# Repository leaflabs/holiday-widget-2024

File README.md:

# Holiday Widget

Basic startup project for NUCLEO-L053R8 board. 

Source code lives in firmware.

The build directory holds all .o files for compliation. The output binary is build/blink.elf. This folder is generated at compilation time and will not exist upon cloning the repository.

Include holds all user created .h files. For the HAL to work, the stm3l0xx_hal_conf_template.h file needs to be copied and adjusted as necessary. No changes were made as of now. 

src holds all user created .c files. This project does not use the c library so some builtin functions needed to be defined, namely __libc_init_array, memset and memcpy. main.c holds the main function and the basic code to blink the LD2 LED at a different speed when the B1 button is pressed.

linker_script.ld defines how the binary should be setup.  
  
Makefile has two main targets: build/blink.elf and upload  
build/blink.elf is also called by just calling 'make' and creates the .elf file. upload sends the .elf file to the Nucleo board.

The STM32CubeL0 and SmallPrintf folders are submodules for this repo. When cloning the project, run 'git submodule update --init --recursive' to create the folder.

Overall steps to get project and upload to nucleo board:
```
git clone --recursive <repo name> 
git submodule update --init --recursive
make
make upload
```

Dependencies:
* STM32CubeL0 at version v1.12.2
* eyalroz/printf at version v6.2.0-b1

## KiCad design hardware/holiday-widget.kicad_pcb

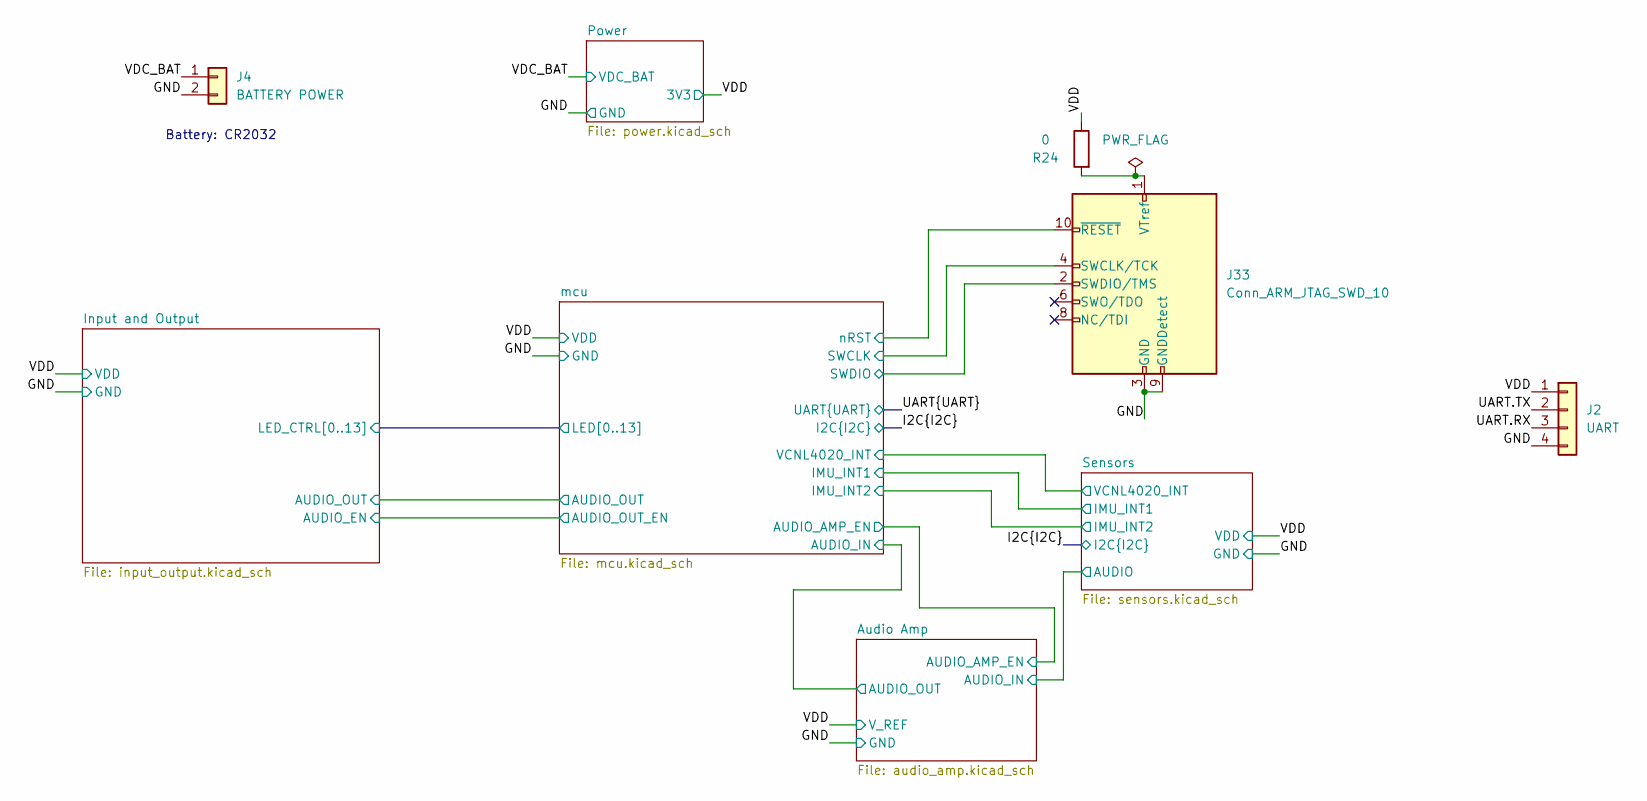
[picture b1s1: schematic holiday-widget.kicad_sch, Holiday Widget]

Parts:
J2: UART; PinHeader_1x04_P2.00mm_Vertical
J4: BATTERY POWER; MPD_BC2032-E2
J33: Conn_ARM_JTAG_SWD_10; PinHeader_2x05_P1.27mm_Vertical
R24: 0; R_0402_1005Metric; MPN RC0402JR-070RL

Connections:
/GND: J2.4, J4.2, J33.3 (GND), J33.5 (GND), J33.9 (GNDDetect); also elsewhere on the board
/UART.RX: J2.3; also elsewhere on the board
/UART.TX: J2.2; also elsewhere on the board
/VDC_BAT: J4.1; also elsewhere on the board
/VDD: J2.1, R24.1; also elsewhere on the board
/mcu/SWCLK: J33.4 (SWCLK/TCK); also elsewhere on the board
/mcu/SWDIO: J33.2 (SWDIO/TMS); also elsewhere on the board
/mcu/nRST: J33.10 (~RESET); also elsewhere on the board
unnamed: J33.1 (VTref), R24.2

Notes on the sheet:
Battery: CR2032

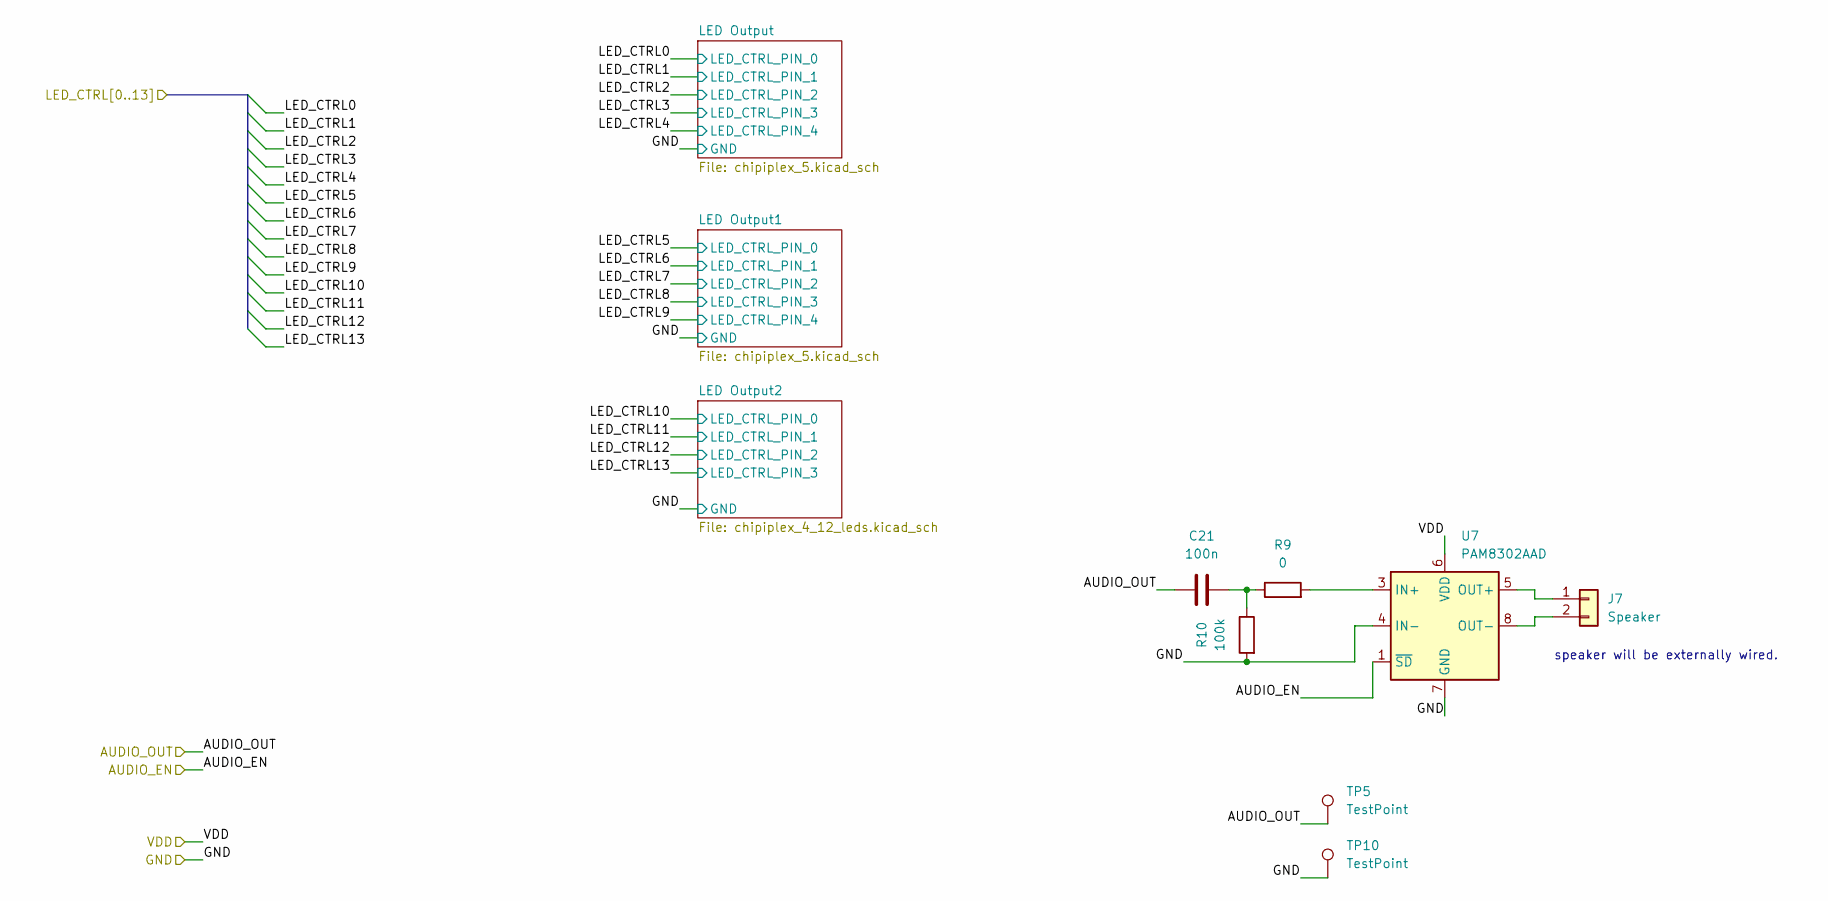
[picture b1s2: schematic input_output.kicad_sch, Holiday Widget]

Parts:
C21: 100n; C_0402_1005Metric; MPN CL05A104KA5NNNC
J7: Speaker; SPKR_AST-01508MR-WT-R
R9: 0; R_0402_1005Metric; MPN RC0402JR-070RL
R10: 100k; R_0402_1005Metric; MPN RC0402FR-07100KL
TP5, TP10: TestPoint; TestPoint_0.5mm_1mm
U7: PAM8302AAD; SSOP-8_2.95x2.8mm_P0.65mm; MPN PAM8302AADCR

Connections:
/GND: R10.2, TP10.1, U7.4 (IN-), U7.7 (GND); also elsewhere on the board
/Input and Output/AUDIO_EN: U7.1 (~SD); also elsewhere on the board
/Input and Output/AUDIO_OUT: C21.1, TP5.1; also elsewhere on the board
/VDD: U7.6 (VDD); also elsewhere on the board
unnamed: C21.2, R9.1, R10.1
unnamed: J7.1, U7.5 (OUT+)
unnamed: J7.2, U7.8 (OUT-)
unnamed: R9.2, U7.3 (IN+)

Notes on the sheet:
speaker will be externally wired.

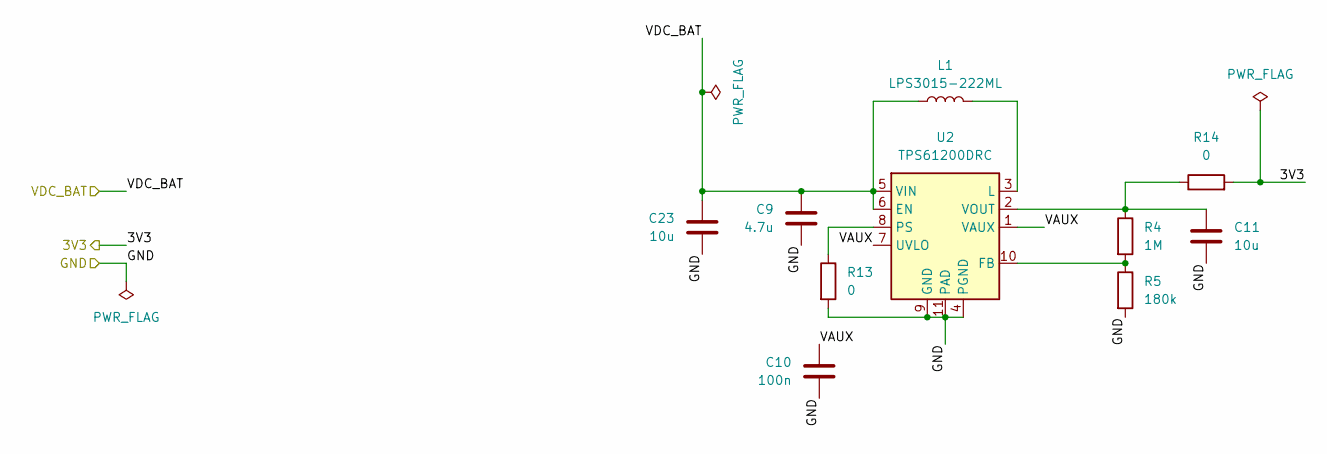
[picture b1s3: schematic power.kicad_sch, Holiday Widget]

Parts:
C9: 4.7u; C_0402_1005Metric; MPN CL05A475MP5NRNC
C10: 100n; C_0402_1005Metric; MPN CL05A104KA5NNNC
C11, C23: 10u; C_0603_1608Metric_Pad1.08x0.95mm_HandSolder; MPN CL10A106MQ8NNNC
L1: LPS3015-222ML; L_Coilcraft_LPS3010; MPN LPS3015-222MRC
R4: 1M; R_0402_1005Metric; MPN RC0402FR-071ML
R5: 180k; R_0402_1005Metric; MPN RC0402JR-07180KL
R13, R14: 0; R_0402_1005Metric; MPN RC0402JR-070RL
U2: TPS61200DRC; Texas_S-PVSON-N10_ThermalVias; MPN TPS61200DRCT

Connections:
/GND: C9.2, C10.2, C11.2, C23.2, R5.2, R13.2, U2.4 (PGND), U2.9 (GND), U2.11 (PAD); also elsewhere on the board
/Power/VAUX: C10.1, U2.1 (VAUX), U2.7 (UVLO)
/VDC_BAT: C9.1, C23.1, L1.1, U2.5 (VIN), U2.6 (EN); also elsewhere on the board
/VDD: R14.2; also elsewhere on the board
unnamed: R4.2, R5.1, U2.10 (FB)
unnamed: L1.2, U2.3 (L)
unnamed: R13.1, U2.8 (PS)
unnamed: C11.1, R4.1, R14.1, U2.2 (VOUT)

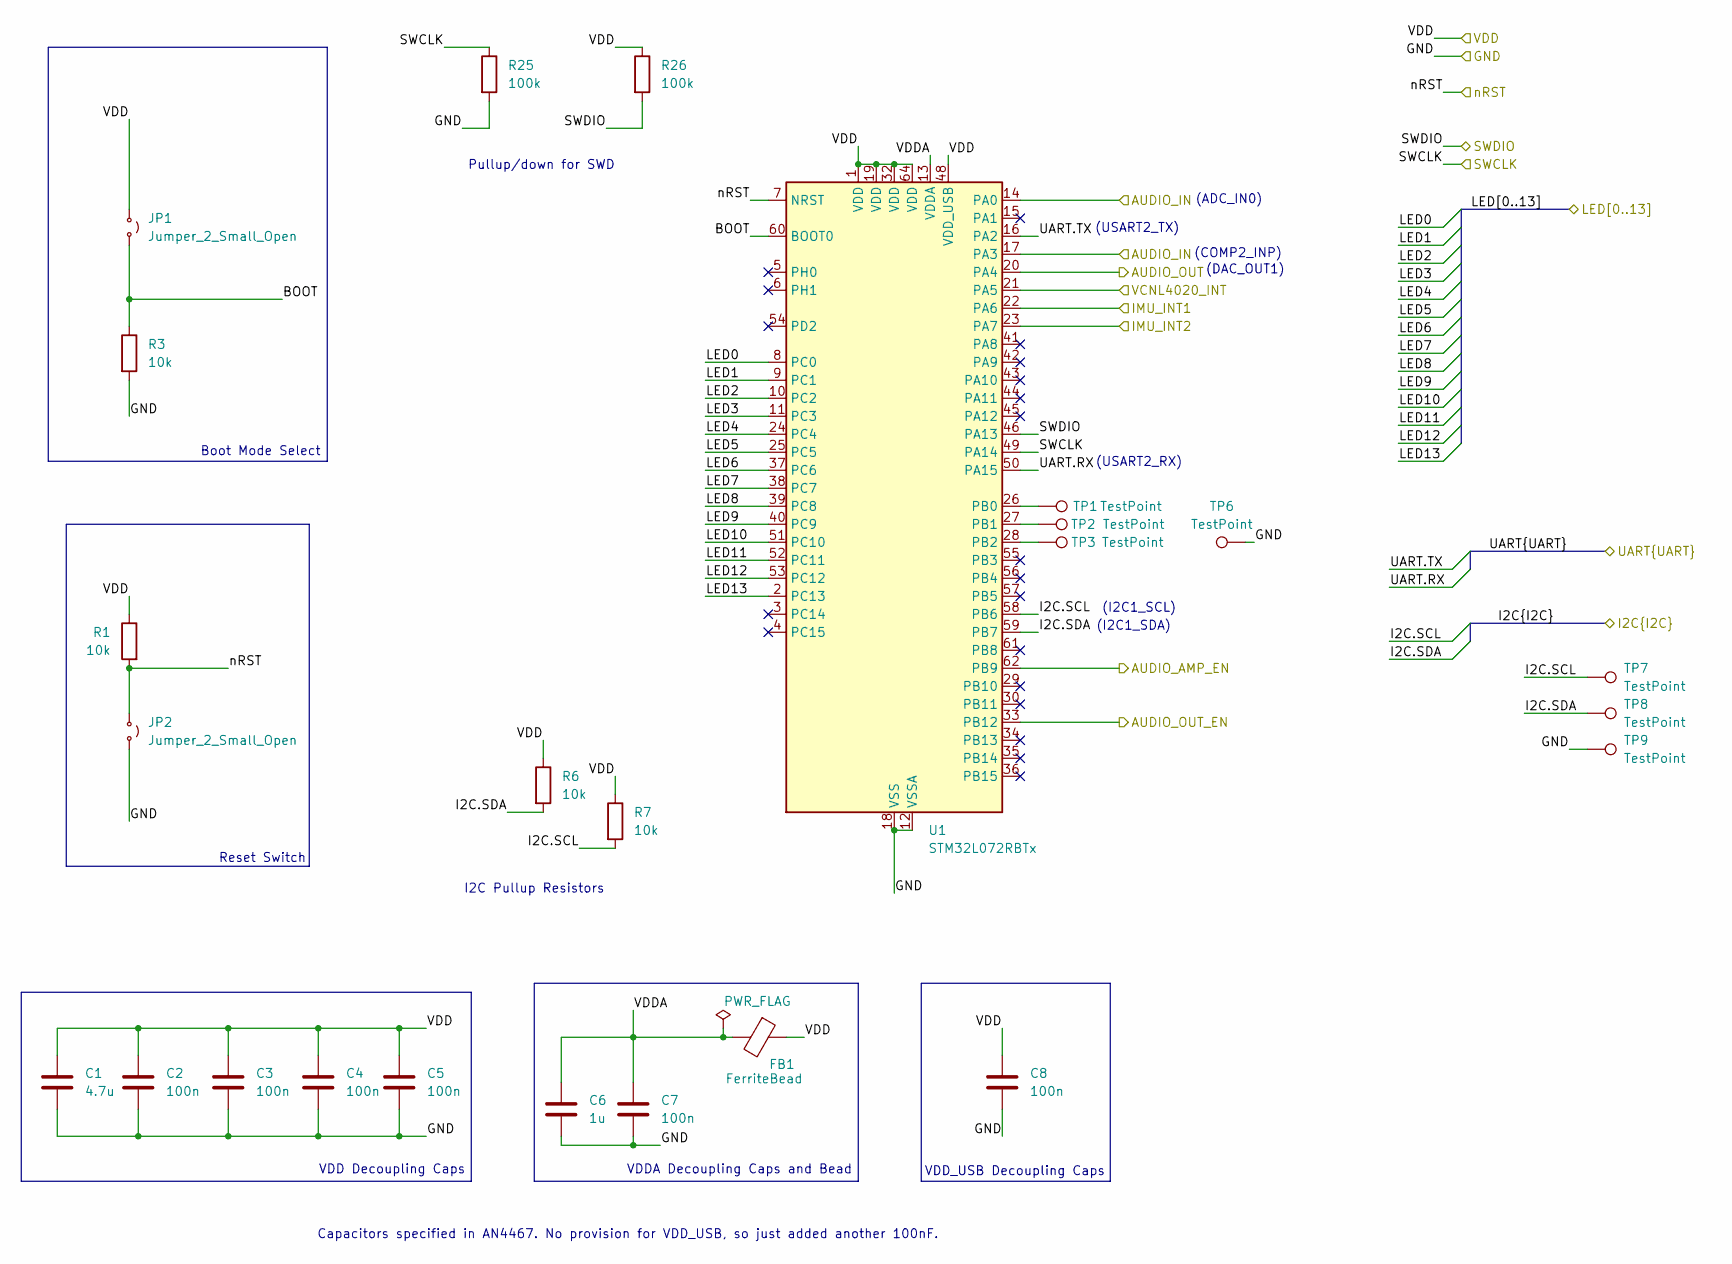
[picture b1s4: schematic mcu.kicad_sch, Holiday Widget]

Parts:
C1: 4.7u; C_0402_1005Metric; MPN CL05A475MP5NRNC
C2, C3, C4, C5, C7, C8: 100n; C_0402_1005Metric; MPN CL05A104KA5NNNC
C6: 1u; C_0603_1608Metric_Pad1.08x0.95mm_HandSolder; MPN CL05A105KO5NNNC
FB1: FerriteBead; C_0603_1608Metric_Pad1.08x0.95mm_HandSolder; MPN 742792662
JP1, JP2: Jumper_2_Small_Open; SolderJumper-2_P1.3mm_Open_RoundedPad1.0x1.5mm
R1, R3, R6, R7: 10k; R_0402_1005Metric; MPN RC0402FR-0710KL
R25, R26: 100k; R_0402_1005Metric; MPN RC0402FR-07100KL
TP1, TP2, TP3, TP6, TP7, TP8, TP9: TestPoint; TestPoint_0.5mm_1mm
U1: STM32L072RBTx; LQFP-64_10x10mm_P0.5mm; MPN STM32L072RBT6

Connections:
/Audio Amp/AUDIO_AMP_EN: U1.62 (PB9); also elsewhere on the board
/Audio Amp/AUDIO_OUT: U1.14 (PA0), U1.17 (PA3); also elsewhere on the board
/GND: C1.2, C2.2, C3.2, C4.2, C5.2, C6.2, C7.2, C8.2, JP2.2 (B), R3.2, R25.2, TP6.1, TP9.1, U1.12 (VSSA), U1.18 (VSS), U1.31 (VSS), U1.47 (VSS), U1.63 (VSS); also elsewhere on the board
/I2C.SCL: R7.2, TP7.1, U1.58 (PB6); also elsewhere on the board
/I2C.SDA: R6.2, TP8.1, U1.59 (PB7); also elsewhere on the board
/Input and Output/AUDIO_EN: U1.33 (PB12); also elsewhere on the board
/Input and Output/AUDIO_OUT: U1.20 (PA4); also elsewhere on the board
/Sensors/IMU_INT1: U1.22 (PA6); also elsewhere on the board
/Sensors/IMU_INT2: U1.23 (PA7); also elsewhere on the board
/Sensors/VCNL4020_INT: U1.21 (PA5); also elsewhere on the board
/UART.RX: U1.50 (PA15); also elsewhere on the board
/UART.TX: U1.16 (PA2); also elsewhere on the board
/VDD: C1.1, C2.1, C3.1, C4.1, C5.1, C8.1, FB1.1, JP1.1 (A), R1.1, R6.1, R7.1, R26.1, U1.1 (VDD), U1.19 (VDD), U1.32 (VDD), U1.48 (VDD_USB), U1.64 (VDD); also elsewhere on the board
/mcu/BOOT: JP1.2 (B), R3.1, U1.60 (BOOT0)
/mcu/LED0: U1.8 (PC0); also elsewhere on the board
/mcu/LED1: U1.9 (PC1); also elsewhere on the board
/mcu/LED2: U1.10 (PC2); also elsewhere on the board
/mcu/LED3: U1.11 (PC3); also elsewhere on the board
/mcu/LED4: U1.24 (PC4); also elsewhere on the board
/mcu/LED5: U1.25 (PC5); also elsewhere on the board
/mcu/LED6: U1.37 (PC6); also elsewhere on the board
/mcu/LED7: U1.38 (PC7); also elsewhere on the board
/mcu/LED8: U1.39 (PC8); also elsewhere on the board
/mcu/LED9: U1.40 (PC9); also elsewhere on the board
/mcu/LED10: U1.51 (PC10); also elsewhere on the board
/mcu/LED11: U1.52 (PC11); also elsewhere on the board
/mcu/LED12: U1.53 (PC12); also elsewhere on the board
/mcu/LED13: U1.2 (PC13); also elsewhere on the board
/mcu/SWCLK: R25.1, U1.49 (PA14); also elsewhere on the board
/mcu/SWDIO: R26.2, U1.46 (PA13); also elsewhere on the board
/mcu/VDDA: C6.1, C7.1, FB1.2, U1.13 (VDDA)
/mcu/nRST: JP2.1 (A), R1.2, U1.7 (NRST); also elsewhere on the board
unnamed: TP1.1, U1.26 (PB0)
unnamed: TP2.1, U1.27 (PB1)
unnamed: TP3.1, U1.28 (PB2)

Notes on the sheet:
Capacitors specified in AN4467. No provision for VDD_USB, so just added another 100nF.
Reset Switch
I2C Pullup Resistors
(COMP2_INP)
VDD_USB Decoupling Caps
VDDA Decoupling Caps and Bead
(ADC_IN0)
(USART2_TX)
Boot Mode Select
Pullup/down for SWD
VDD Decoupling Caps
(I2C1_SCL)
(USART2_RX)
(DAC_OUT1)
(I2C1_SDA)

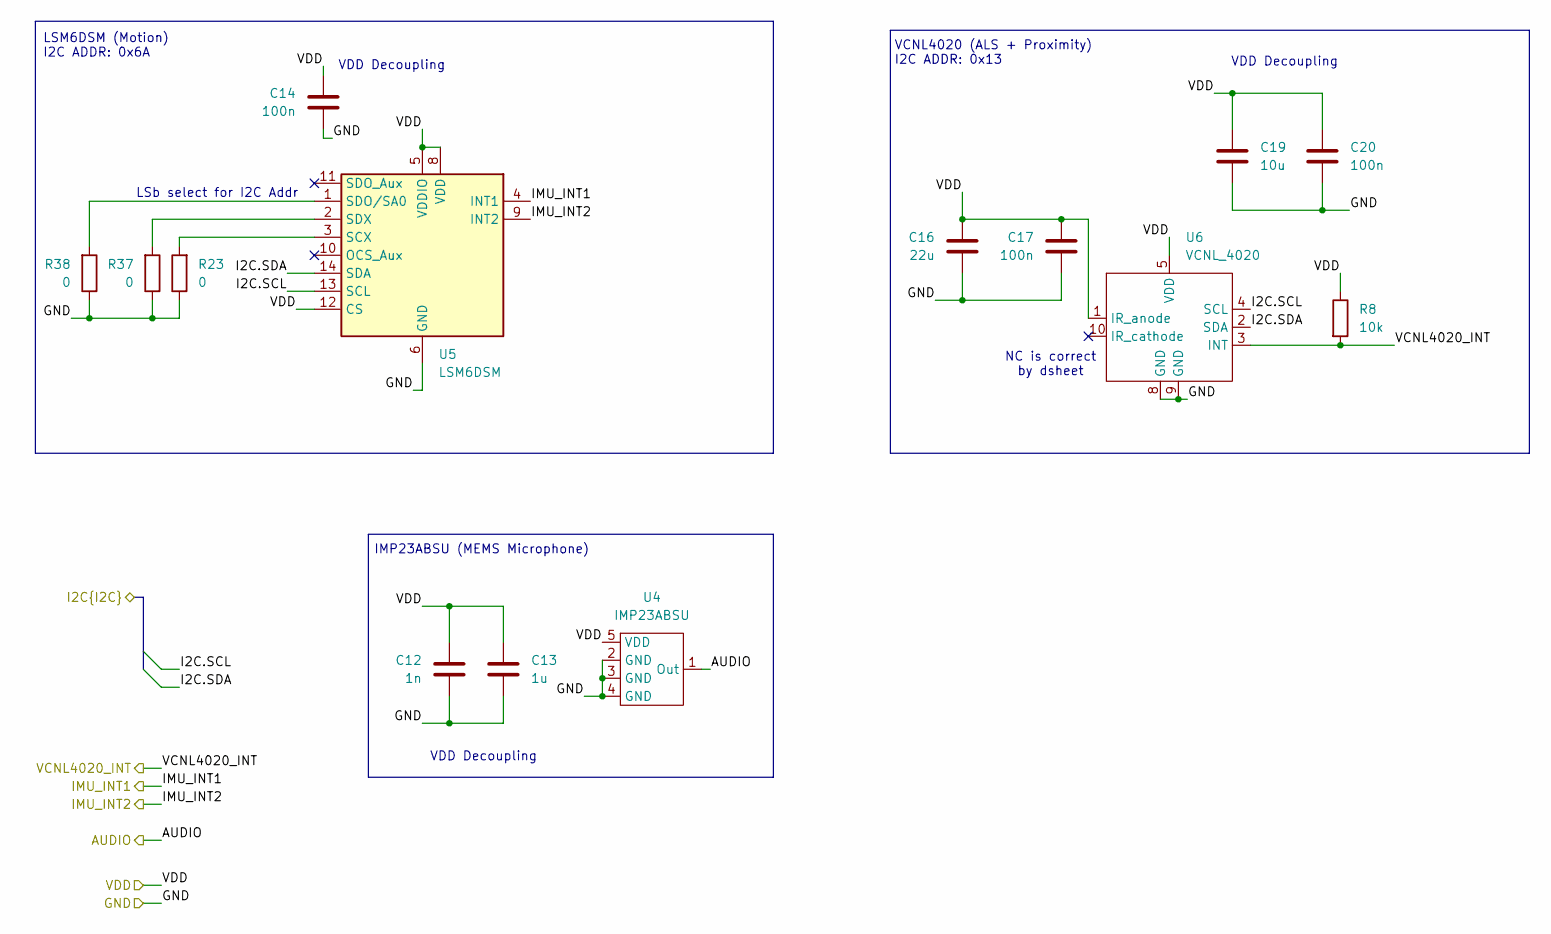
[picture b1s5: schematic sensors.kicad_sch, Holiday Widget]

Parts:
C12: 1n; C_0402_1005Metric; MPN C0402C102K4RACTU
C13: 1u; C_0603_1608Metric_Pad1.08x0.95mm_HandSolder; MPN CL05A105KO5NNNC
C14, C17, C20: 100n; C_0402_1005Metric; MPN CL05A104KA5NNNC
C16: 22u; C_0603_1608Metric_Pad1.08x0.95mm_HandSolder; MPN CL10A226MO7JZNC
C19: 10u; C_0603_1608Metric_Pad1.08x0.95mm_HandSolder; MPN CL10A106MQ8NNNC
R8: 10k; R_0402_1005Metric; MPN RC0402FR-0710KL
R23, R37, R38: 0; R_0402_1005Metric; MPN RC0402JR-070RL
U4: IMP23ABSU; RHLGA5_3P5X2P65X0P98_STM; MPN IMP23ABSUTR
U5: LSM6DSM; LGA-14_3x2.5mm_P0.5mm_LayoutBorder3x4y; MPN LSM6DSMTR
U6: VCNL_4020; VCNL4020_SMD; MPN VCNL4020-GS08

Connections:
/Audio Amp/AUDIO_IN: U4.1 (Out); also elsewhere on the board
/GND: C12.2, C13.2, C14.2, C16.2, C17.2, C19.2, C20.2, R23.1, R37.1, R38.1, U4.2 (GND), U4.3 (GND), U4.4 (GND), U5.6 (GND), U5.7 (GND), U6.8 (GND), U6.9 (GND); also elsewhere on the board
/I2C.SCL: U5.13 (SCL), U6.4 (SCL); also elsewhere on the board
/I2C.SDA: U5.14 (SDA), U6.2 (SDA); also elsewhere on the board
/Sensors/IMU_INT1: U5.4 (INT1); also elsewhere on the board
/Sensors/IMU_INT2: U5.9 (INT2); also elsewhere on the board
/Sensors/VCNL4020_INT: R8.2, U6.3 (INT); also elsewhere on the board
/VDD: C12.1, C13.1, C14.1, C16.1, C17.1, C19.1, C20.1, R8.1, U4.5 (VDD), U5.5 (VDDIO), U5.8 (VDD), U5.12 (CS), U6.1 (IR_anode), U6.5 (VDD); also elsewhere on the board
unnamed: R23.2, U5.3 (SCX)
unnamed: R38.2, U5.1 (SDO/SA0)
unnamed: R37.2, U5.2 (SDX)

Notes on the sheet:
IMP23ABSU (MEMS Microphone)
LSb select for I2C Addr
VDD Decoupling
NC is correct by dsheet
LSM6DSM (Motion) I2C ADDR: 0x6A
VCNL4020 (ALS + Proximity) I2C ADDR: 0x13

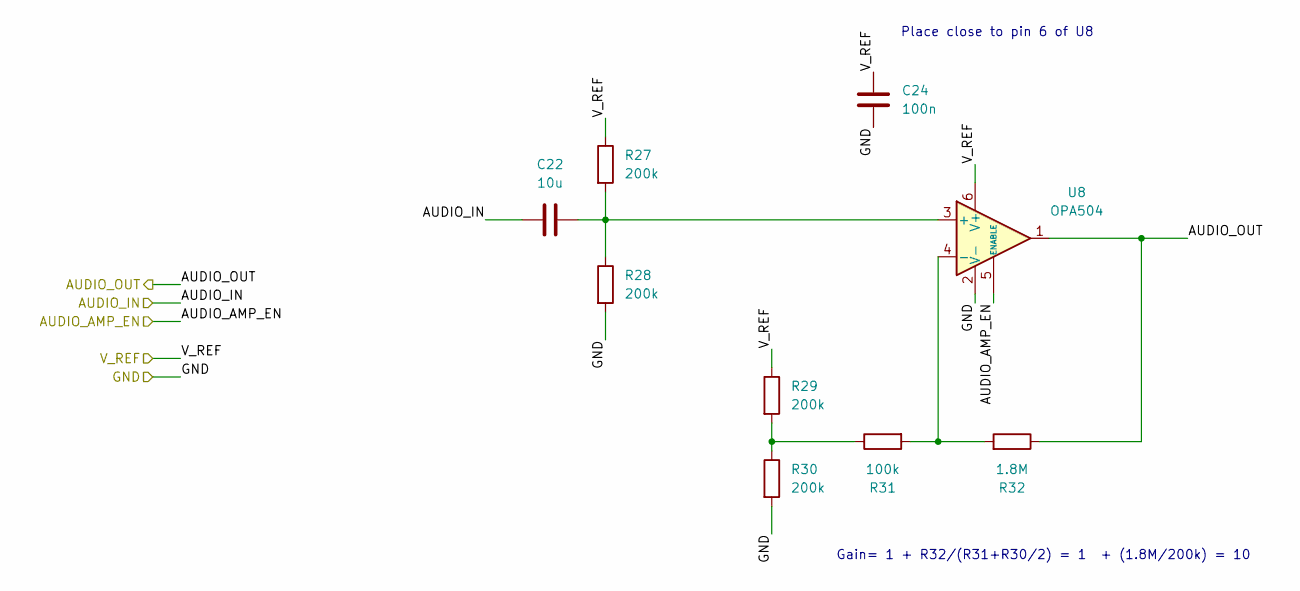
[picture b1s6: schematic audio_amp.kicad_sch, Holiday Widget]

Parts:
C22: 10u; C_0603_1608Metric_Pad1.08x0.95mm_HandSolder; MPN CL10A106MQ8NNNC
C24: 100n; C_0402_1005Metric; MPN CL05A104KA5NNNC
R27, R28, R29, R30: 200k; R_0402_1005Metric; MPN RC0402FR-07200KL
R31: 100k; R_0402_1005Metric; MPN RC0402FR-07100KL
R32: 1.8M; R_0402_1005Metric; MPN RC0402JR-071M8L
U8: OPA504; SOT-23-6

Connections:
/Audio Amp/AUDIO_AMP_EN: U8.5 (ENABLE); also elsewhere on the board
/Audio Amp/AUDIO_IN: C22.1; also elsewhere on the board
/Audio Amp/AUDIO_OUT: R32.1, U8.1; also elsewhere on the board
/GND: C24.1, R28.2, R30.2, U8.2 (V-); also elsewhere on the board
/VDD: C24.2, R27.1, R29.1, U8.6 (V+); also elsewhere on the board
unnamed: R29.2, R30.1, R31.1
unnamed: C22.2, R27.2, R28.1, U8.3 (+)
unnamed: R31.2, R32.2, U8.4 (-)

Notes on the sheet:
Gain= 1 + R32/(R31+R30/2) = 1 + (1.8M/200k) = 10
Place close to pin 6 of U8

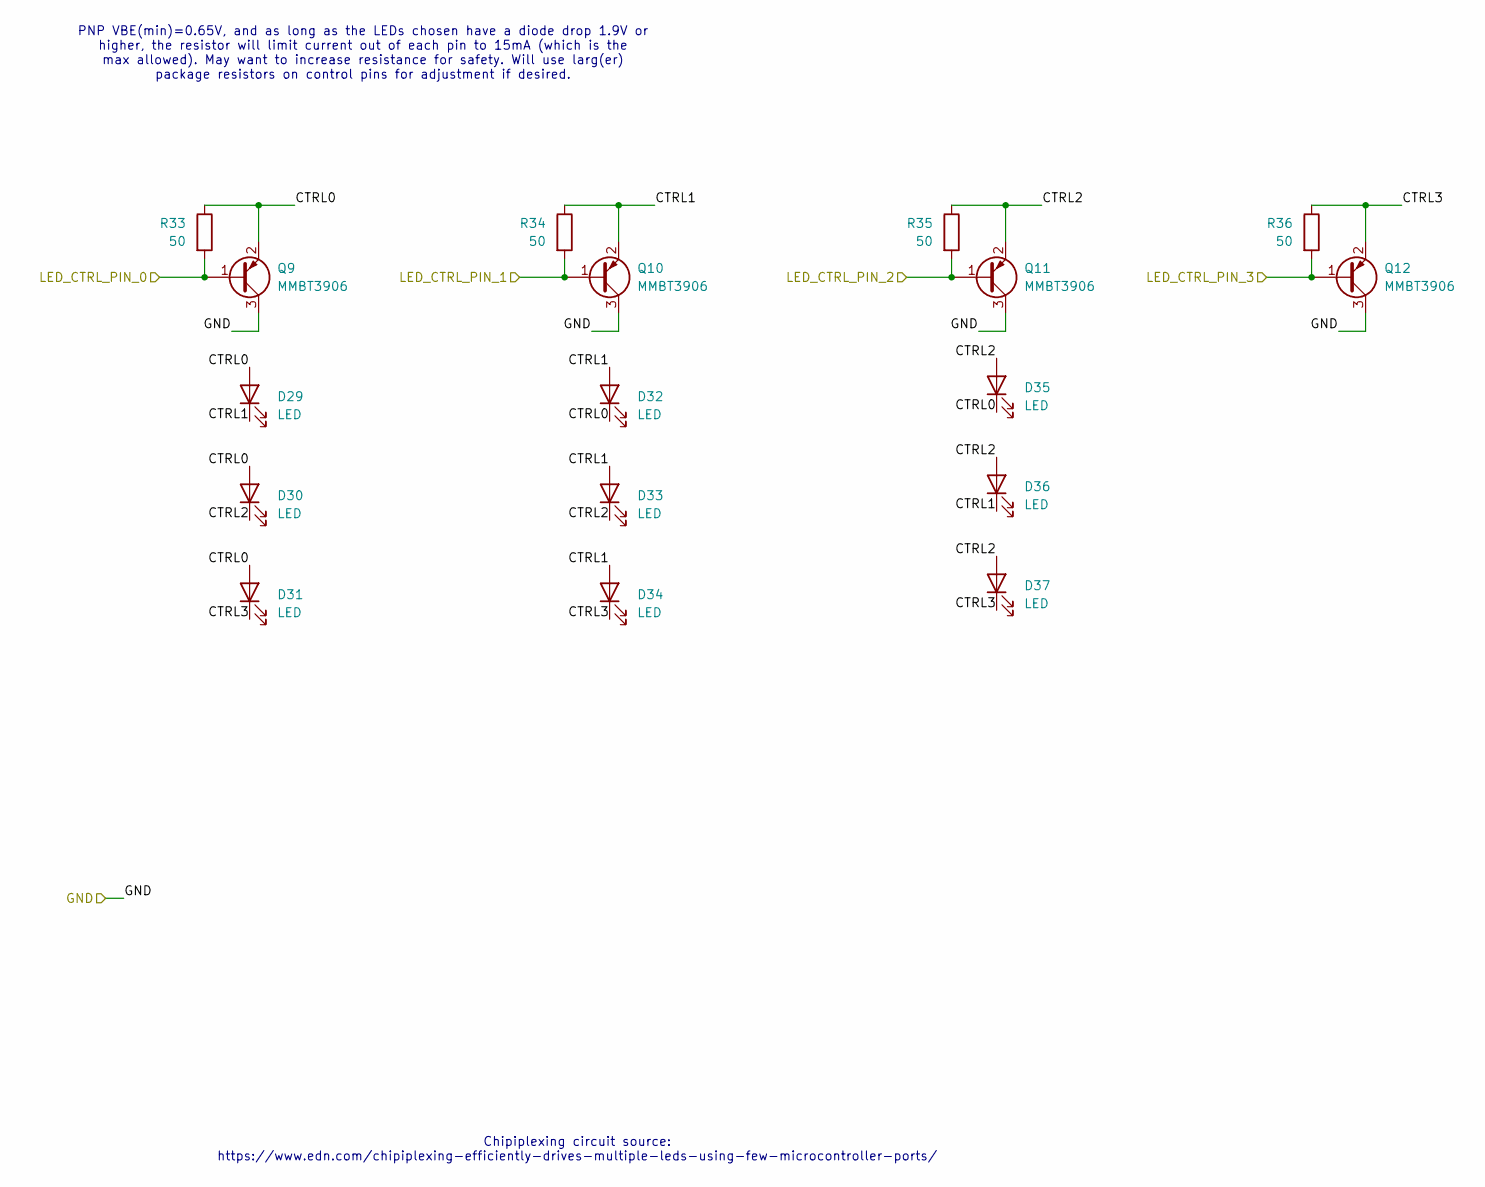
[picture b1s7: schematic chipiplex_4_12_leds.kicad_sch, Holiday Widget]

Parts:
D29, D30, D31, D32, D33, D34, D35, D36, D37: LED; LED_0805_2012Metric_Pad1.15x1.40mm_HandSolder; MPN LTST-C171GKT
Q9, Q10, Q11, Q12: MMBT3906; SOT-23; MPN MMBT3906
R33, R34, R35, R36: 50; R_0402_1005Metric; MPN RC0402JR-0750RL

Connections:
/GND: Q9.3 (C), Q10.3 (C), Q11.3 (C), Q12.3 (C); also elsewhere on the board
/Input and Output/LED Output2/CTRL0: D29.2 (A), D30.2 (A), D31.2 (A), D32.1 (K), D35.1 (K), Q9.2 (E), R33.1
/Input and Output/LED Output2/CTRL1: D29.1 (K), D32.2 (A), D33.2 (A), D34.2 (A), D36.1 (K), Q10.2 (E), R34.1
/Input and Output/LED Output2/CTRL2: D30.1 (K), D33.1 (K), D35.2 (A), D36.2 (A), D37.2 (A), Q11.2 (E), R35.1
/Input and Output/LED Output2/CTRL3: D31.1 (K), D34.1 (K), D37.1 (K), Q12.2 (E), R36.1
/mcu/LED10: Q9.1 (B), R33.2; also elsewhere on the board
/mcu/LED11: Q10.1 (B), R34.2; also elsewhere on the board
/mcu/LED12: Q11.1 (B), R35.2; also elsewhere on the board
/mcu/LED13: Q12.1 (B), R36.2; also elsewhere on the board

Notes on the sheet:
Chipiplexing circuit source: https://www.edn.com/chipiplexing-efficiently-drives-multiple-leds-using-few-microcontroller-ports/
PNP VBE(min)=0.65V, and as long as the LEDs chosen have a diode drop 1.9V or higher, the resistor will limit current out of each pin to 15mA (which is the max allowed). May want to increase resistance for safety. Will use larg(er) package resistors on control pins for adjustment if desired.

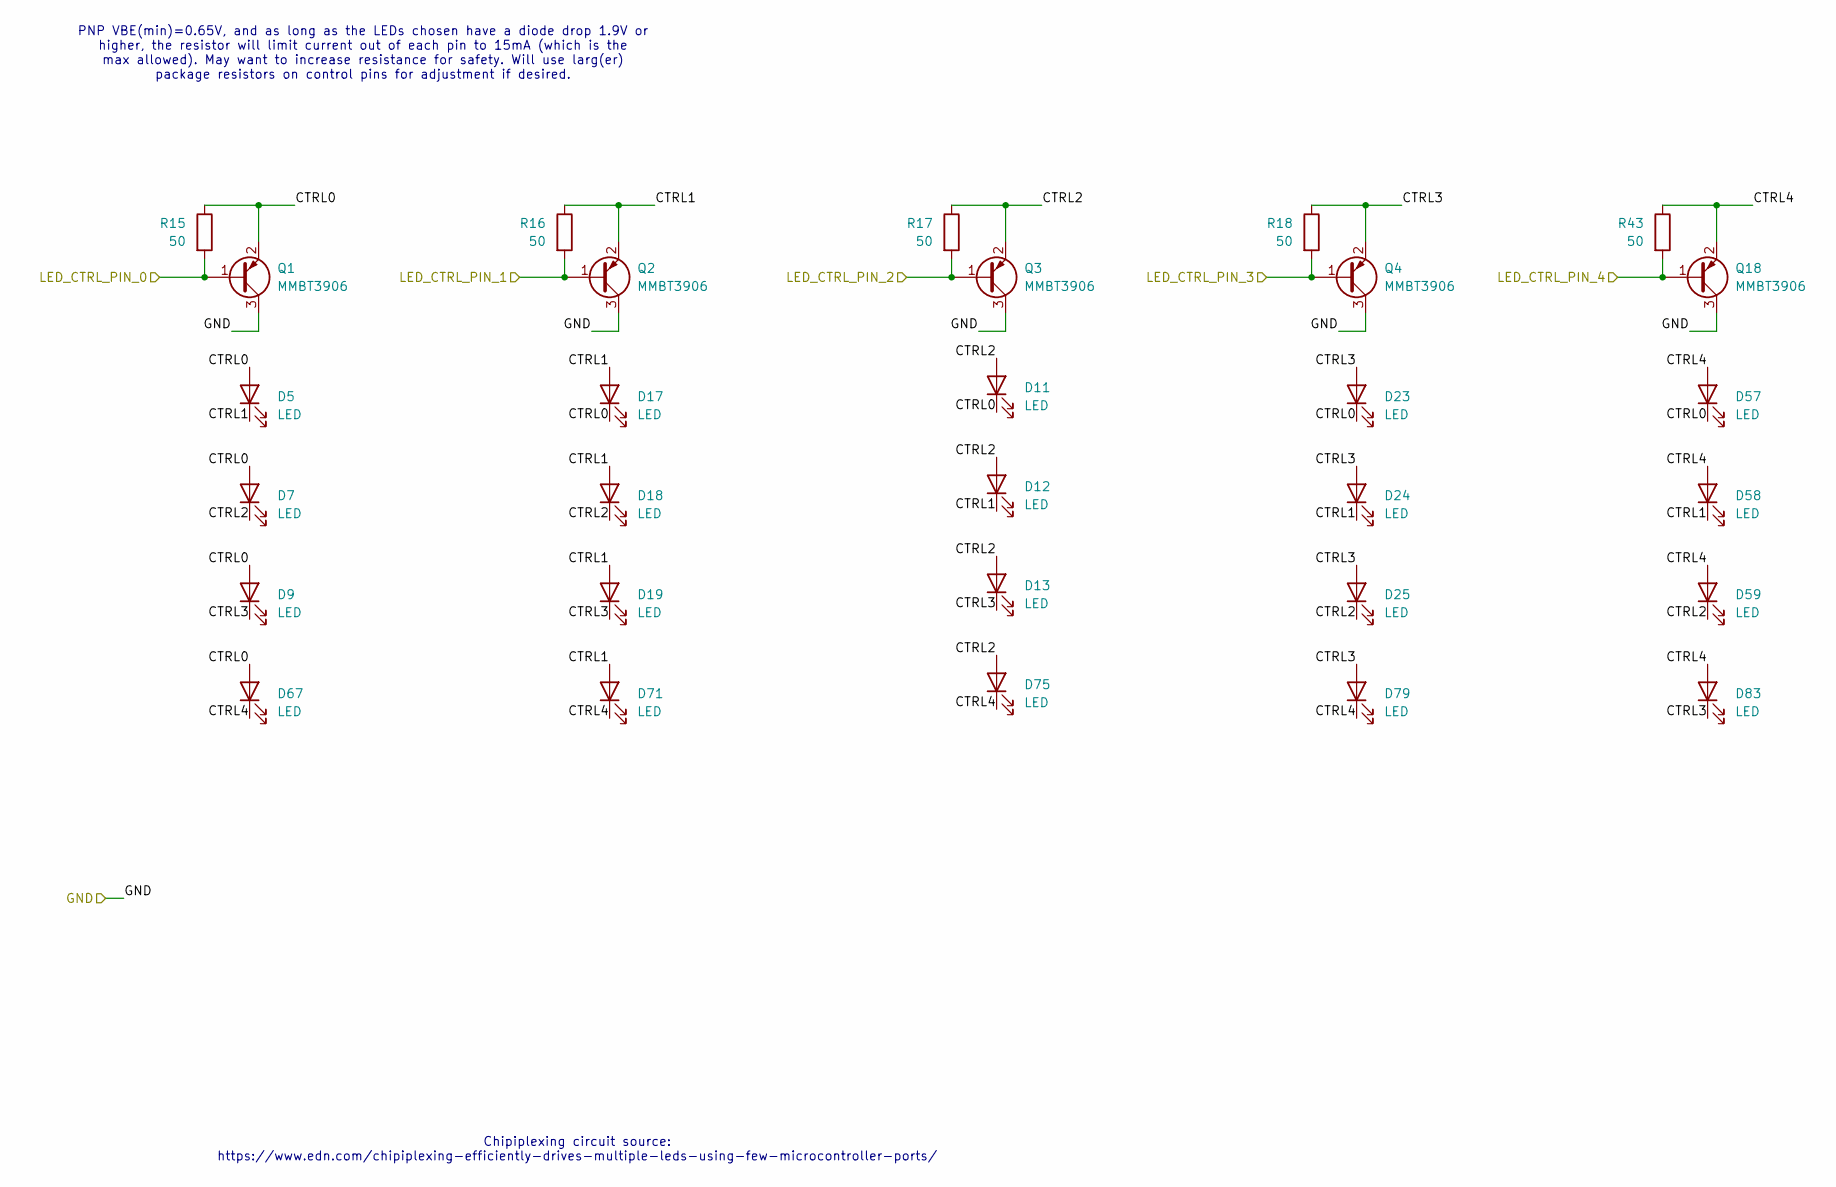
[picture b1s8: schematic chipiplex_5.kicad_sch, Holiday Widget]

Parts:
D5, D7, D9, D11, D12, D13, D17, D18, D19, D23, D24, D25, D57, D58, D59, D67, D71, D75, D79, D83: LED; LED_0805_2012Metric_Pad1.15x1.40mm_HandSolder; MPN LTST-C171GKT
Q1, Q2, Q3, Q4, Q18: MMBT3906; SOT-23; MPN MMBT3906
R15, R16, R17, R18, R43: 50; R_0402_1005Metric; MPN RC0402JR-0750RL

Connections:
/GND: Q1.3 (C), Q2.3 (C), Q3.3 (C), Q4.3 (C), Q18.3 (C); also elsewhere on the board
/Input and Output/LED Output/CTRL0: D5.2 (A), D7.2 (A), D9.2 (A), D11.1 (K), D17.1 (K), D23.1 (K), D57.1 (K), D67.2 (A), Q1.2 (E), R15.1
/Input and Output/LED Output/CTRL1: D5.1 (K), D12.1 (K), D17.2 (A), D18.2 (A), D19.2 (A), D24.1 (K), D58.1 (K), D71.2 (A), Q2.2 (E), R16.1
/Input and Output/LED Output/CTRL2: D7.1 (K), D11.2 (A), D12.2 (A), D13.2 (A), D18.1 (K), D25.1 (K), D59.1 (K), D75.2 (A), Q3.2 (E), R17.1
/Input and Output/LED Output/CTRL3: D9.1 (K), D13.1 (K), D19.1 (K), D23.2 (A), D24.2 (A), D25.2 (A), D79.2 (A), D83.1 (K), Q4.2 (E), R18.1
/Input and Output/LED Output/CTRL4: D57.2 (A), D58.2 (A), D59.2 (A), D67.1 (K), D71.1 (K), D75.1 (K), D79.1 (K), D83.2 (A), Q18.2 (E), R43.1
/mcu/LED0: Q1.1 (B), R15.2; also elsewhere on the board
/mcu/LED1: Q2.1 (B), R16.2; also elsewhere on the board
/mcu/LED2: Q3.1 (B), R17.2; also elsewhere on the board
/mcu/LED3: Q4.1 (B), R18.2; also elsewhere on the board
/mcu/LED4: Q18.1 (B), R43.2; also elsewhere on the board

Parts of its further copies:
D6, D8, D10, D14, D15, D16, D20, D21, D22, D26, D27, D28, D60, D61, D62, D68, D72, D76, D80, D84: LED; LED_0805_2012Metric_Pad1.15x1.40mm_HandSolder; MPN LTST-C171GKT
Q5, Q6, Q7, Q8, Q19: MMBT3906; SOT-23; MPN MMBT3906
R19, R20, R21, R22, R44: 50; R_0402_1005Metric; MPN RC0402JR-0750RL

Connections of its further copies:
/GND: Q5.3 (C), Q6.3 (C), Q7.3 (C), Q8.3 (C), Q19.3 (C); also elsewhere on the board
/Input and Output/LED Output1/CTRL0: D6.2 (A), D8.2 (A), D10.2 (A), D14.1 (K), D20.1 (K), D26.1 (K), D60.1 (K), D68.2 (A), Q5.2 (E), R19.1
/Input and Output/LED Output1/CTRL1: D6.1 (K), D15.1 (K), D20.2 (A), D21.2 (A), D22.2 (A), D27.1 (K), D61.1 (K), D72.2 (A), Q6.2 (E), R20.1
/Input and Output/LED Output1/CTRL2: D8.1 (K), D14.2 (A), D15.2 (A), D16.2 (A), D21.1 (K), D28.1 (K), D62.1 (K), D76.2 (A), Q7.2 (E), R21.1
/Input and Output/LED Output1/CTRL3: D10.1 (K), D16.1 (K), D22.1 (K), D26.2 (A), D27.2 (A), D28.2 (A), D80.2 (A), D84.1 (K), Q8.2 (E), R22.1
/Input and Output/LED Output1/CTRL4: D60.2 (A), D61.2 (A), D62.2 (A), D68.1 (K), D72.1 (K), D76.1 (K), D80.1 (K), D84.2 (A), Q19.2 (E), R44.1
/mcu/LED5: Q5.1 (B), R19.2; also elsewhere on the board
/mcu/LED6: Q6.1 (B), R20.2; also elsewhere on the board
/mcu/LED7: Q7.1 (B), R21.2; also elsewhere on the board
/mcu/LED8: Q8.1 (B), R22.2; also elsewhere on the board
/mcu/LED9: Q19.1 (B), R44.2; also elsewhere on the board

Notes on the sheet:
Chipiplexing circuit source: https://www.edn.com/chipiplexing-efficiently-drives-multiple-leds-using-few-microcontroller-ports/
PNP VBE(min)=0.65V, and as long as the LEDs chosen have a diode drop 1.9V or higher, the resistor will limit current out of each pin to 15mA (which is the max allowed). May want to increase resistance for safety. Will use larg(er) package resistors on control pins for adjustment if desired.
